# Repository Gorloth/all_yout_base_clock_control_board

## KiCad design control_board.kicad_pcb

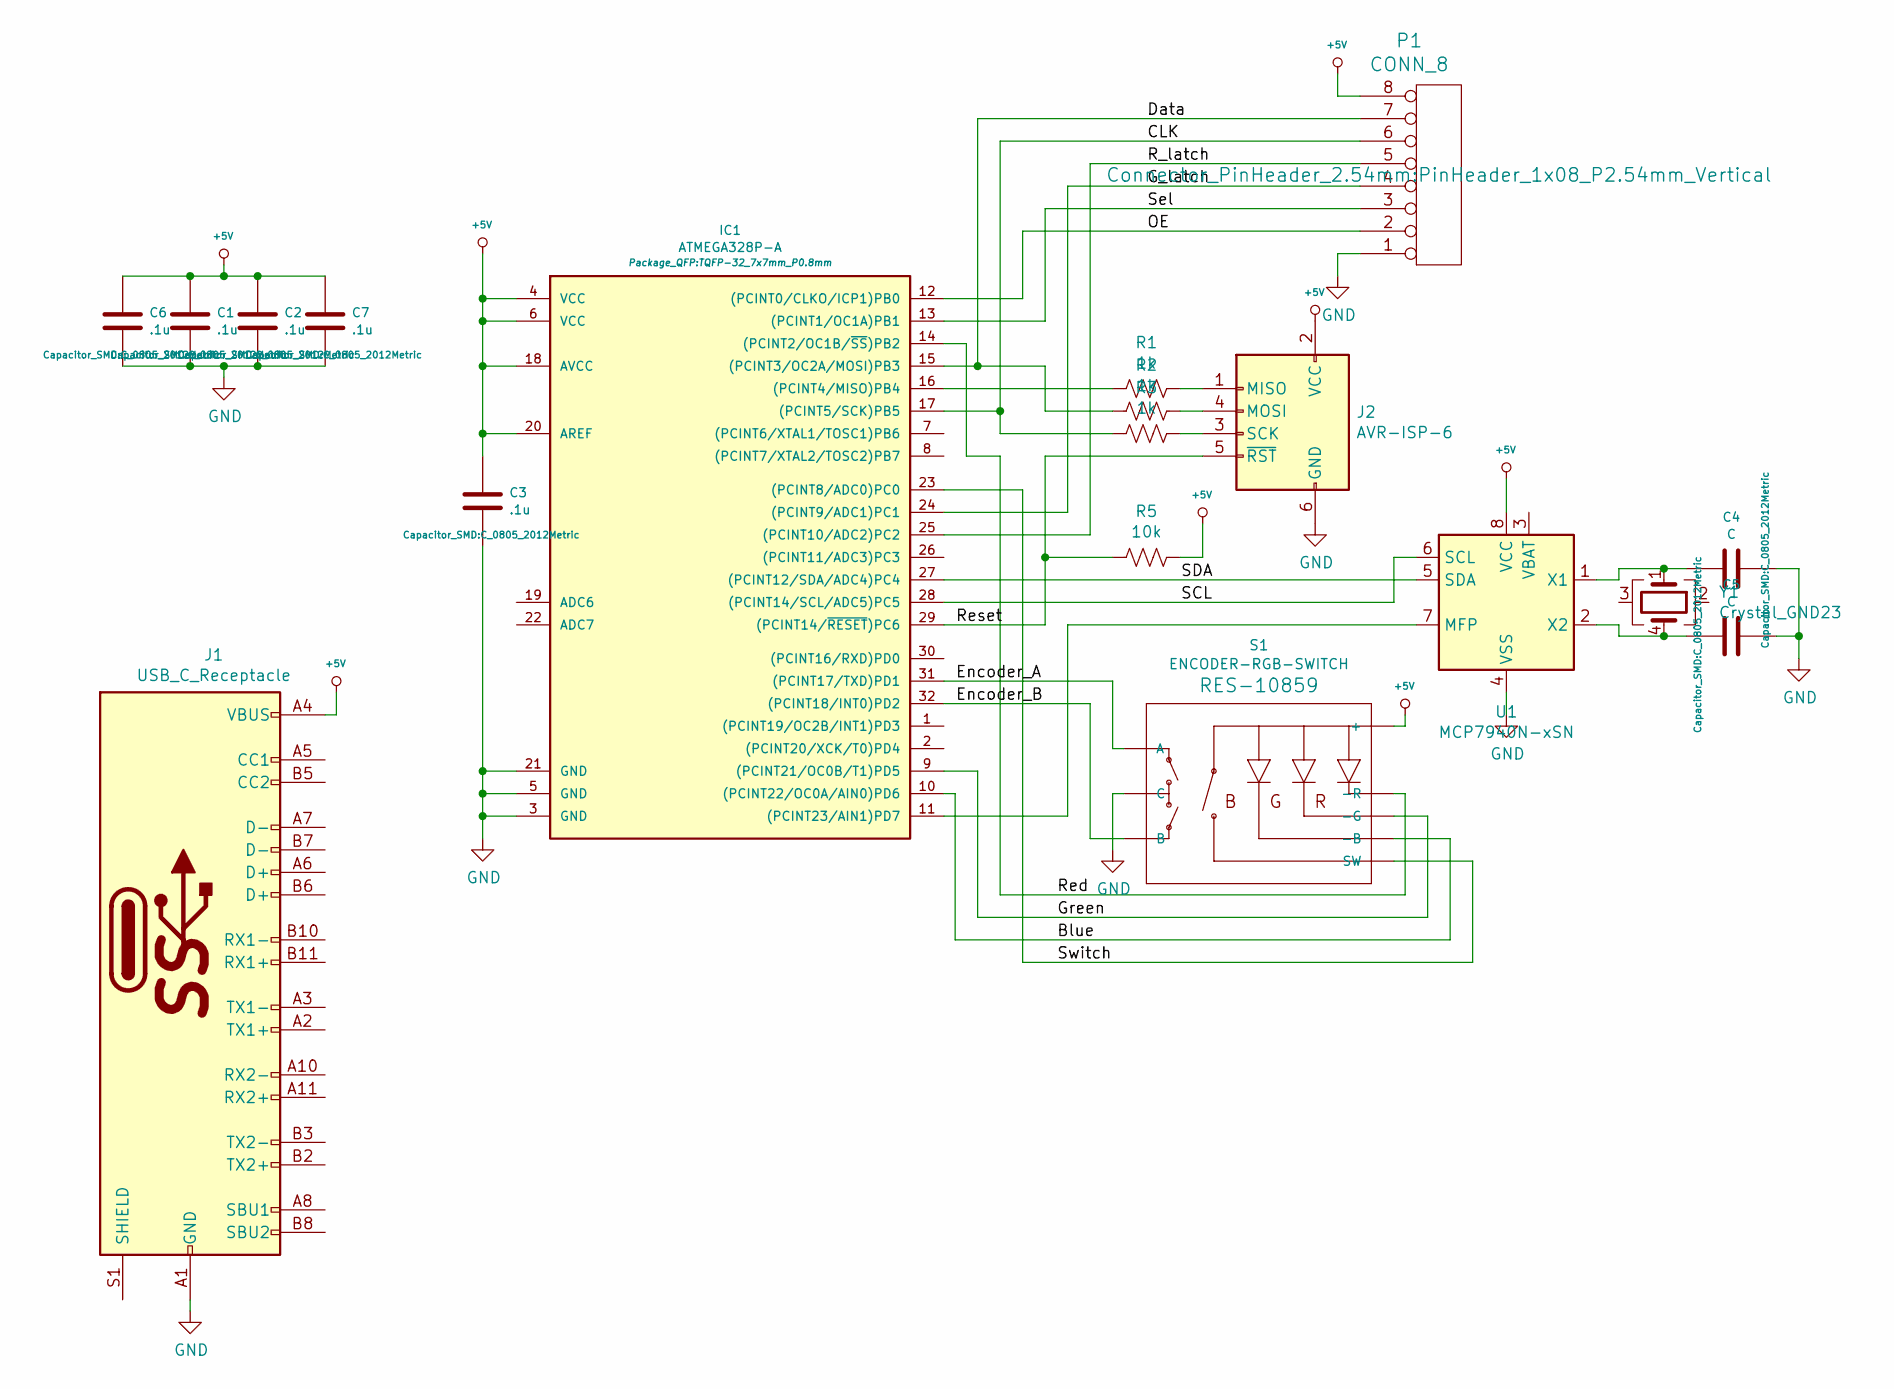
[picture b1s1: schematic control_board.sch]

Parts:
C1, C2, C3, C6, C7: .1u; C_0805_2012Metric
C4, C5: C; C_0805_2012Metric
IC1: ATMEGA328P-A; TQFP-32_7x7mm_P0.8mm
J1: USB_C_Receptacle; JAE_DX07S024XJ1R1100
J2: AVR-ISP-6; PinHeader_2x03_P2.54mm_Vertical
P1: CONN_8; PinHeader_1x08_P2.54mm_Vertical
R1, R2, R3: 1k; R_0805_2012Metric
R5: 10k; R_0805_2012Metric
S1: ENCODER-RGB-SWITCH; Encoder_w_switch_RGB_LED_SMD
U1: MCP7940N-xSN; SSOP-8_3.95x5.21x3.27mm_P1.27mm
Y1: Crystal_GND23; Crystal_SMD_SeikoEpson_MC146-4Pin_6.7x1.5mm_HandSoldering

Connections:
+5V: C1.1, C2.1, C3.1, C6.1, C7.1, IC1.4 (VCC), IC1.6 (VCC), IC1.18 (AVCC), IC1.20 (AREF), J1.A4 (VBUS), J1.A9 (VBUS), J1.B4 (VBUS), J1.B9 (VBUS), J2.2 (VCC), P1.8, R5.1, S1.5 (+), U1.8 (VCC)
/Blue: IC1.10 ((PCINT22/OC0A/AIN0)PD6), S1.4 (-B)
/CLK: IC1.17 ((PCINT5/SCK)PB5), P1.6, R3.2
/Data: IC1.15 ((PCINT3/OC2A/MOSI)PB3), P1.7, R2.2
/Encoder_A: IC1.31 ((PCINT17/TXD)PD1), S1.A
/Encoder_B: IC1.32 ((PCINT18/INT0)PD2), S1.B
/G_latch: IC1.24 ((PCINT9/ADC1)PC1), P1.4
/Green: IC1.9 ((PCINT21/OC0B/T1)PD5), S1.2 (-G)
/OE: IC1.12 ((PCINT0/CLKO/ICP1)PB0), P1.2
/R_latch: IC1.25 ((PCINT10/ADC2)PC2), P1.5
/Red: IC1.14 ((PCINT2/OC1B/~SS~)PB2), S1.1 (-R)
/Reset: IC1.29 ((PCINT14/~RESET~)PC6), J2.5 (~RST), R5.2
/SCL: IC1.28 ((PCINT14/SCL/ADC5)PC5), U1.6 (SCL)
/SDA: IC1.27 ((PCINT12/SDA/ADC4)PC4), U1.5 (SDA)
/Sel: IC1.13 ((PCINT1/OC1A)PB1), P1.3
/Switch: IC1.23 ((PCINT8/ADC0)PC0), S1.3 (SW)
GND: C1.2, C2.2, C3.2, C4.2, C5.1, C6.2, C7.2, IC1.3 (GND), IC1.5 (GND), IC1.21 (GND), J1.A1 (GND), J1.A12 (GND), J1.B1 (GND), J1.B12 (GND), J2.6 (GND), P1.1, S1.C, U1.4 (VSS)
unnamed: C4.1, U1.1 (X1), Y1.1
unnamed: C5.2, U1.2 (X2), Y1.4
unnamed: IC1.11 ((PCINT23/AIN1)PD7), U1.7 (MFP)
unnamed: IC1.16 ((PCINT4/MISO)PB4), R1.2
unnamed: J2.1 (MISO), R1.1
unnamed: J2.3 (SCK), R3.1
unnamed: J2.4 (MOSI), R2.1

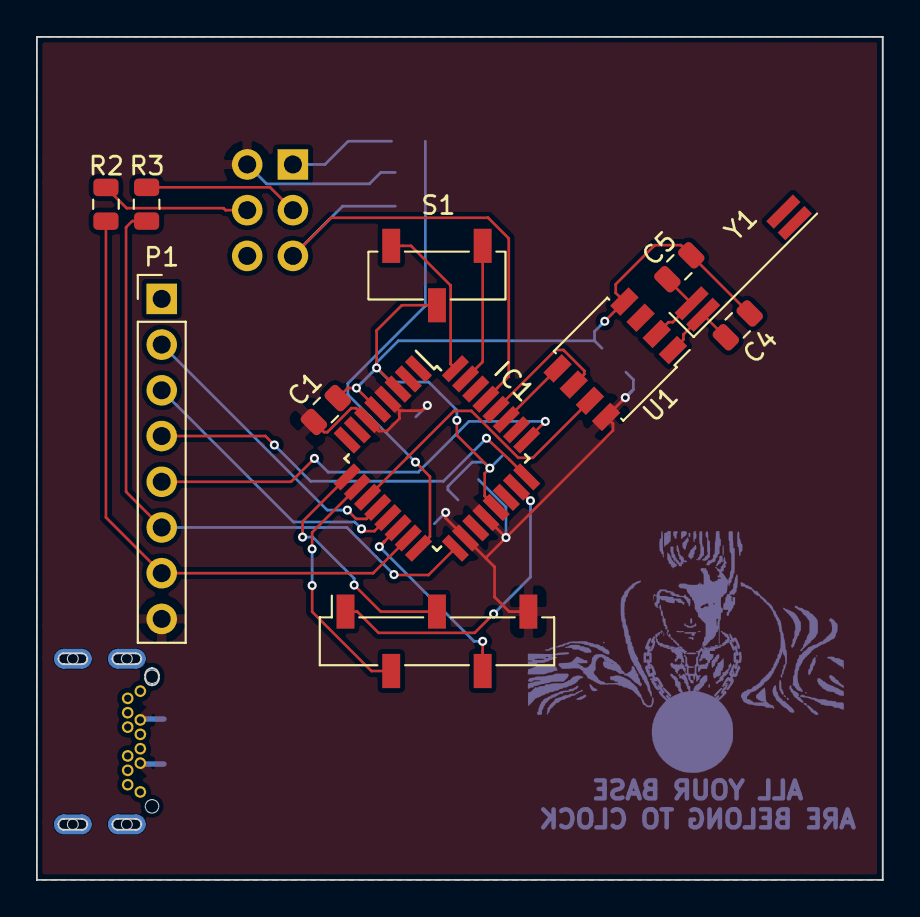
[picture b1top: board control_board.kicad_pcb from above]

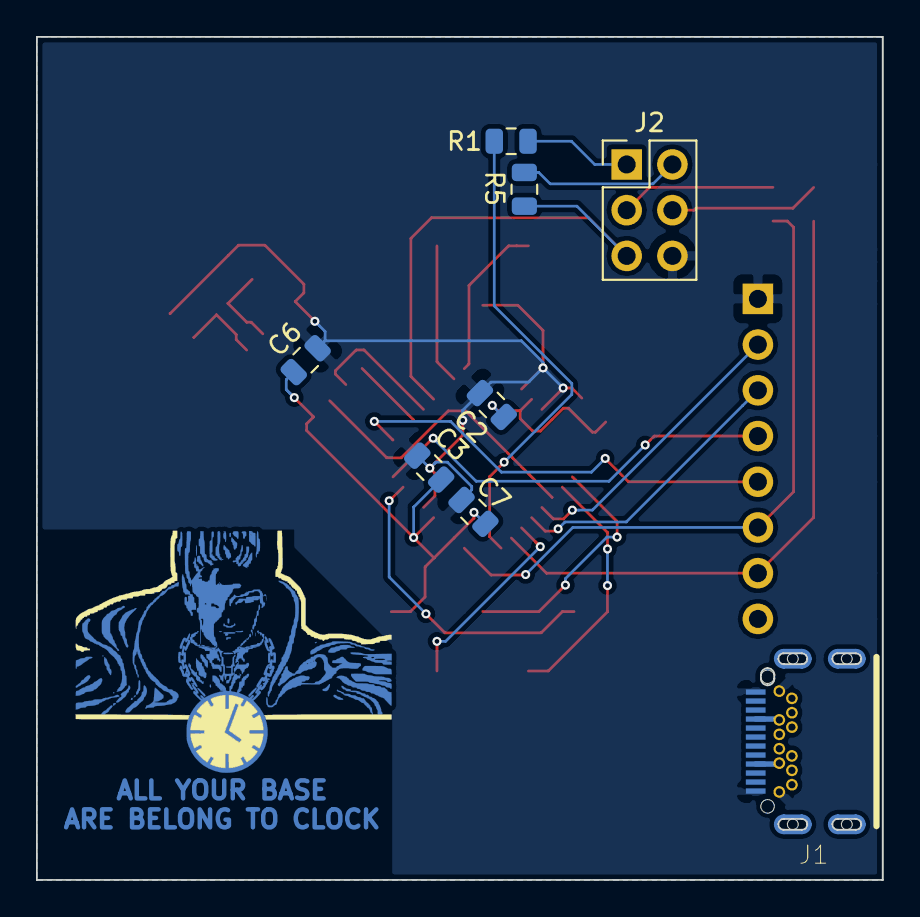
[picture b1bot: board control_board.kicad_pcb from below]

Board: 2 copper layers, 47.0 x 46.8 mm, 18 parts (8 on the bottom side), 24 nets.

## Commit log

2019-01-06 Rev 1 of the control board
2019-01-07 Update for board rev 2
    Move USB connector to board edge
    Move resisters to not interfere with programming header
    Widen board to fit enclosure
    Move programming header and USB connector away from top/bottom of board for more clearance with enclosure
    Move red encoder LED to a PWM capable pin
